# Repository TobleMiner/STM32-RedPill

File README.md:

STM32 RedPill
=============

The RedPill, for when you realize the BluePill just doesn't cut it.

The RedPill is designed as a more powerful drop-in replacement for the
BluePill. While .1" wider the RedPill is fully pin-compatible to the
BluePill.  
The following table summarizes the most important differences between
RedPill and BluePill:  
|                  | RedPill       | BluePill         |
|------------------|---------------|------------------|
| MCU              | STM32F722REC6 | STM32F103C8T6    |
| ARM core         | Cortex-M7     | Cortex-M3        |
| Max system clock | 216MHz        | 72MHz            |
| Flash            | 256kB         | 128kB            |
| SRAM             | 256kB         | 20kB             |
| Programming      | DFU, SWD      | SWD              |
| USB connector    | USB Type C    | Micro USB Type B |
| SD card          | MicroSD       | -                |
| LEDs             | 5             | 1                |

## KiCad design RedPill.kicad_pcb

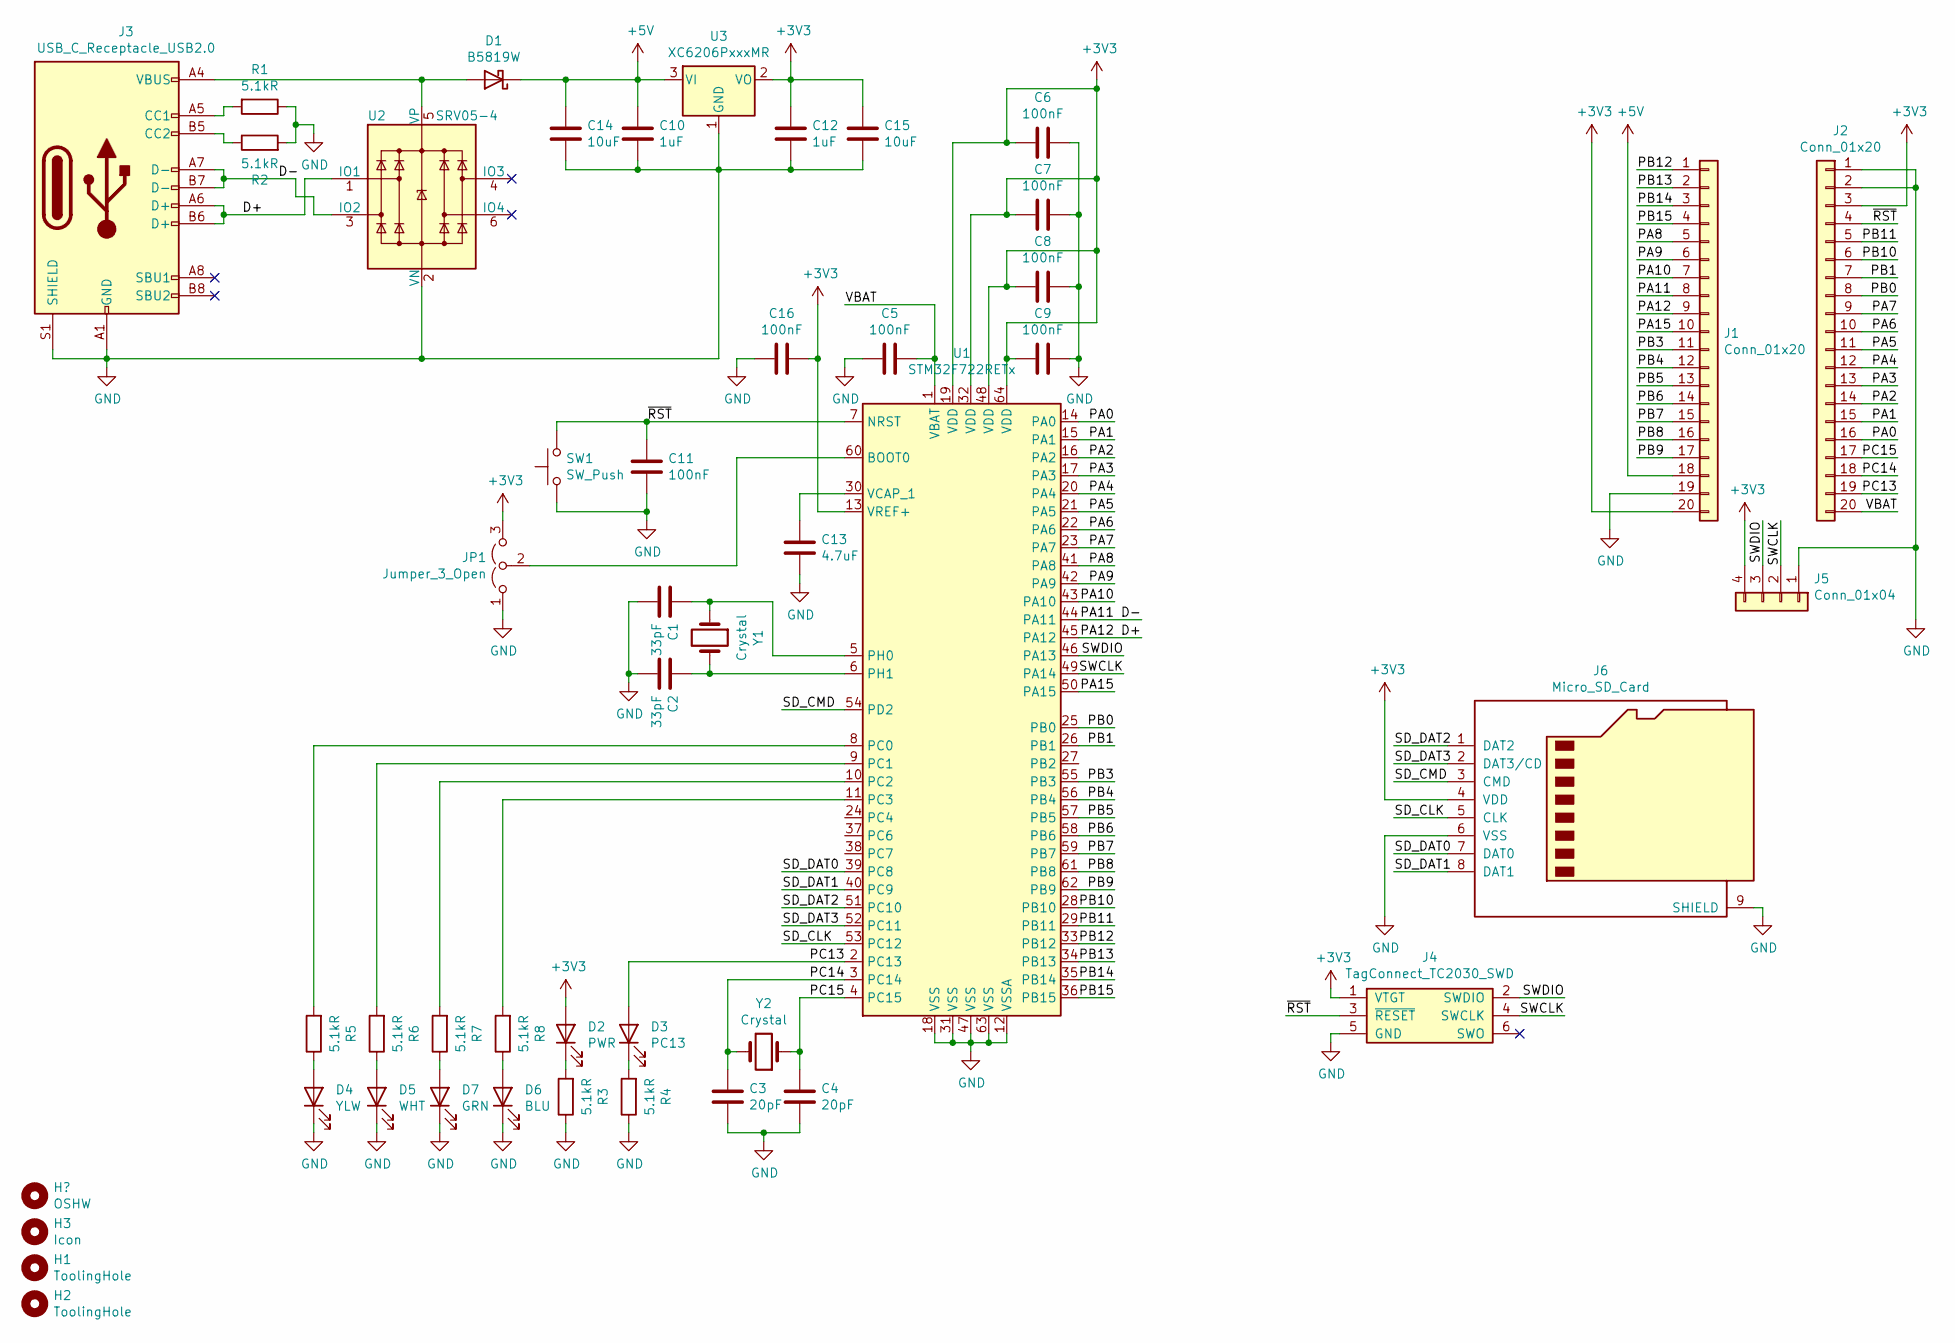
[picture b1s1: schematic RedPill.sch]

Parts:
C1, C2: 33pF; C_0402_1005Metric; LCSC C1562
C3, C4: 20pF; C_0402_1005Metric; LCSC C1554
C5, C6, C7, C8, C9, C11, C16: 100nF; C_0402_1005Metric; LCSC C1525
C10, C12: 1uF; C_0402_1005Metric; LCSC C52923
C13: 4.7uF; C_0402_1005Metric; LCSC C23733
C14: 10uF; C_0603_1608Metric; LCSC C19702
C15: 10uF; C_0402_1005Metric; LCSC C15525
D1: B5819W; D_SOD-123; LCSC C8598
D2: PWR; LED_0603_1608Metric; LCSC C2286
D3: PC13; LED_0603_1608Metric; LCSC C2286
D4: YLW; LED_0603_1608Metric; LCSC C72038
D5: WHT; LED_0603_1608Metric; LCSC C2290
D6: BLU; LED_0603_1608Metric; LCSC C72041
D7: GRN; LED_0603_1608Metric; LCSC C72043
H1, H2: ToolingHole; ToolingHole_JLCSMT
H3: Icon; pill
J1, J2: Conn_01x20; PinHeader_1x20_P2.54mm_Vertical
J3: USB_C_Receptacle_USB2.0; USB_C_Receptacle_Palconn_UTC16-G
J4: TagConnect_TC2030_SWD; Tag-Connect_TC2030-IDC-NL_2x03_P1.27mm_Vertical
J5: Conn_01x04; PinHeader_1x04_P2.54mm_Horizontal
J6: Micro_SD_Card; XUNPU_TF.104
JP1: Jumper_3_Open; PinHeader_1x03_P2.54mm_Vertical
R1, R2, R3, R4, R5, R6, R7, R8: 5.1kR; R_0402_1005Metric; LCSC C25905
SW1: SW_Push; TS-1187A-X-X-X; LCSC C318889
U1: STM32F722RETx; LQFP-64_10x10mm_P0.5mm; LCSC C118207
U2: SRV05-4; SOT-23-6; LCSC C85364
U3: XC6206PxxxMR; SOT-23; LCSC C5446
Y1: Crystal; Crystal_SMD_5032-2Pin_5.0x3.2mm; LCSC C115962
Y2: Crystal; Crystal_SMD_3215-2Pin_3.2x1.5mm; LCSC C32346

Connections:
+3V3: C6.1, C7.1, C8.1, C9.1, C12.1, C15.1, C16.2, D2.2 (A), J1.20, J2.3, J4.1 (VTGT), J5.4, J6.4 (VDD), JP1.3 (B), U1.13 (VREF+), U1.19 (VDD), U1.32 (VDD), U1.48 (VDD), U1.64 (VDD), U3.2 (VO)
+5V: C10.1, C14.1, D1.1 (K), J1.18, U3.3 (VI)
/D+: J1.9, J3.A6 (D+), J3.B6 (D+), U1.45 (PA12), U2.1 (IO1)
/D-: J1.8, J3.A7 (D-), J3.B7 (D-), U1.44 (PA11), U2.3 (IO2)
/PA0: J2.16, U1.14 (PA0)
/PA1: J2.15, U1.15 (PA1)
/PA2: J2.14, U1.16 (PA2)
/PA3: J2.13, U1.17 (PA3)
/PA4: J2.12, U1.20 (PA4)
/PA5: J2.11, U1.21 (PA5)
/PA6: J2.10, U1.22 (PA6)
/PA7: J2.9, U1.23 (PA7)
/PA8: J1.5, U1.41 (PA8)
/PA9: J1.6, U1.42 (PA9)
/PA10: J1.7, U1.43 (PA10)
/PA15: J1.10, U1.50 (PA15)
/PB0: J2.8, U1.25 (PB0)
/PB1: J2.7, U1.26 (PB1)
/PB3: J1.11, U1.55 (PB3)
/PB4: J1.12, U1.56 (PB4)
/PB5: J1.13, U1.57 (PB5)
/PB6: J1.14, U1.58 (PB6)
/PB7: J1.15, U1.59 (PB7)
/PB8: J1.16, U1.61 (PB8)
/PB9: J1.17, U1.62 (PB9)
/PB10: J2.6, U1.28 (PB10)
/PB11: J2.5, U1.29 (PB11)
/PB12: J1.1, U1.33 (PB12)
/PB13: J1.2, U1.34 (PB13)
/PB14: J1.3, U1.35 (PB14)
/PB15: J1.4, U1.36 (PB15)
/PC13: D3.2 (A), J2.19, U1.2 (PC13)
/PC14: C3.1, J2.18, U1.3 (PC14), Y2.2
/PC15: C4.1, J2.17, U1.4 (PC15), Y2.1
/SD_CLK: J6.5 (CLK), U1.53 (PC12)
/SD_CMD: J6.3 (CMD), U1.54 (PD2)
/SD_DAT0: J6.7 (DAT0), U1.39 (PC8)
/SD_DAT1: J6.8 (DAT1), U1.40 (PC9)
/SD_DAT2: J6.1 (DAT2), U1.51 (PC10)
/SD_DAT3: J6.2 (DAT3/CD), U1.52 (PC11)
/SWCLK: J4.4 (SWCLK), J5.2, U1.49 (PA14)
/SWDIO: J4.2 (SWDIO), J5.3, U1.46 (PA13)
/VBAT: C5.2, J2.20, U1.1 (VBAT)
/~RST: C11.1, J2.4, J4.3 (~RESET), SW1.2, U1.7 (NRST)
GND: C1.2, C2.2, C3.2, C4.2, C5.1, C6.2, C7.2, C8.2, C9.2, C10.2, C11.2, C12.2, C13.2, C14.2, C15.2, C16.1, D4.1 (K), D5.1 (K), D6.1 (K), D7.1 (K), J1.19, J2.1, J2.2, J3.A1 (GND), J3.A12 (GND), J3.B1 (GND), J3.B12 (GND), J3.S1 (SHIELD), J4.5 (GND), J5.1, J6.6 (VSS), J6.9 (SHIELD), JP1.1 (A), R1.1, R2.2, R3.1, R4.1, SW1.1, U1.12 (VSSA), U1.18 (VSS), U1.31 (VSS), U1.47 (VSS), U1.63 (VSS), U2.2 (VN), U3.1 (GND)
unnamed: C1.1, U1.5 (PH0), Y1.1
unnamed: C2.1, U1.6 (PH1), Y1.2
unnamed: C13.1, U1.30 (VCAP_1)
unnamed: D1.2 (A), J3.A4 (VBUS), J3.A9 (VBUS), J3.B4 (VBUS), J3.B9 (VBUS), U2.5 (VP)
unnamed: D2.1 (K), R3.2
unnamed: D3.1 (K), R4.2
unnamed: D4.2 (A), R5.1
unnamed: D5.2 (A), R6.1
unnamed: D6.2 (A), R8.1
unnamed: D7.2 (A), R7.1
unnamed: J3.A5 (CC1), R1.2
unnamed: J3.B5 (CC2), R2.1
unnamed: JP1.2 (C), U1.60 (BOOT0)
unnamed: R5.2, U1.8 (PC0)
unnamed: R6.2, U1.9 (PC1)
unnamed: R7.2, U1.10 (PC2)
unnamed: R8.2, U1.11 (PC3)

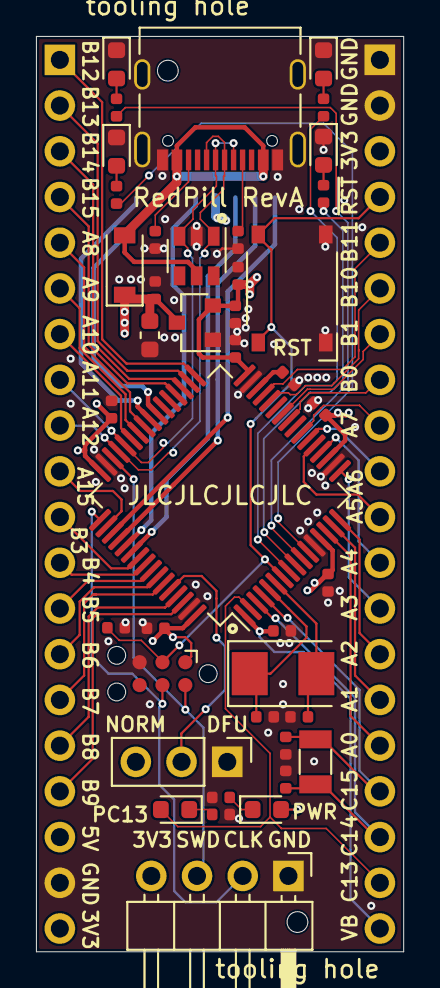
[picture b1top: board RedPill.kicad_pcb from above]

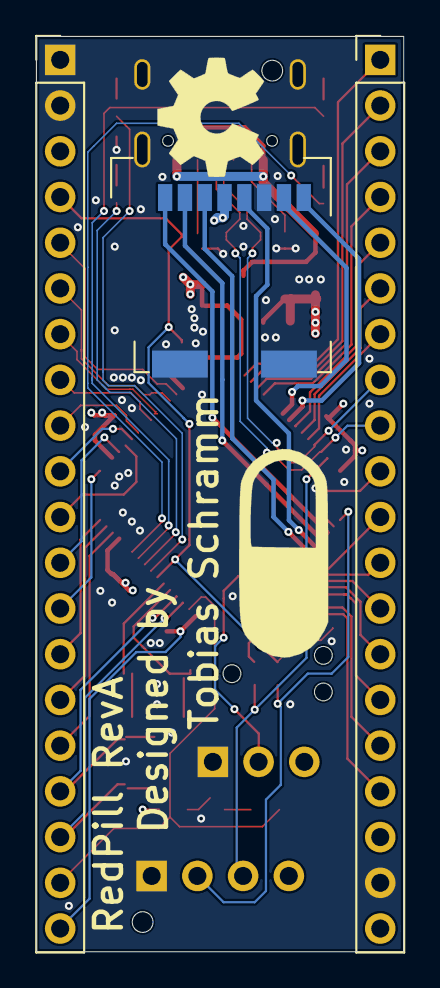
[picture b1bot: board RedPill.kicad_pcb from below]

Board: 4 copper layers, 20.4 x 50.9 mm, 48 parts (5 on the bottom side), 62 nets.

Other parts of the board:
H4: OSHW; OSHW-Symbol_6.7x6mm_SilkScreen

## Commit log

2020-09-28 Hide all fp references
2020-09-28 Route IOs
2020-09-28 Finish layout
2020-09-28 Add JLCSMT tooling holes
2020-09-28 Add silkscreen markings
2020-09-28 Add OSHW logo
2020-09-28 Add LICENSE
2020-09-28 Add chip orientation markings
2020-09-28 Attach 5V pin to input capacitor
2020-09-28 Add LCSC partnumbers to all components
    Yes, even ones JLC can not populate
2020-09-28 Add README
2020-09-28 Add RevA fabrication files
2020-09-28 Ignore 3rdparty libraries
